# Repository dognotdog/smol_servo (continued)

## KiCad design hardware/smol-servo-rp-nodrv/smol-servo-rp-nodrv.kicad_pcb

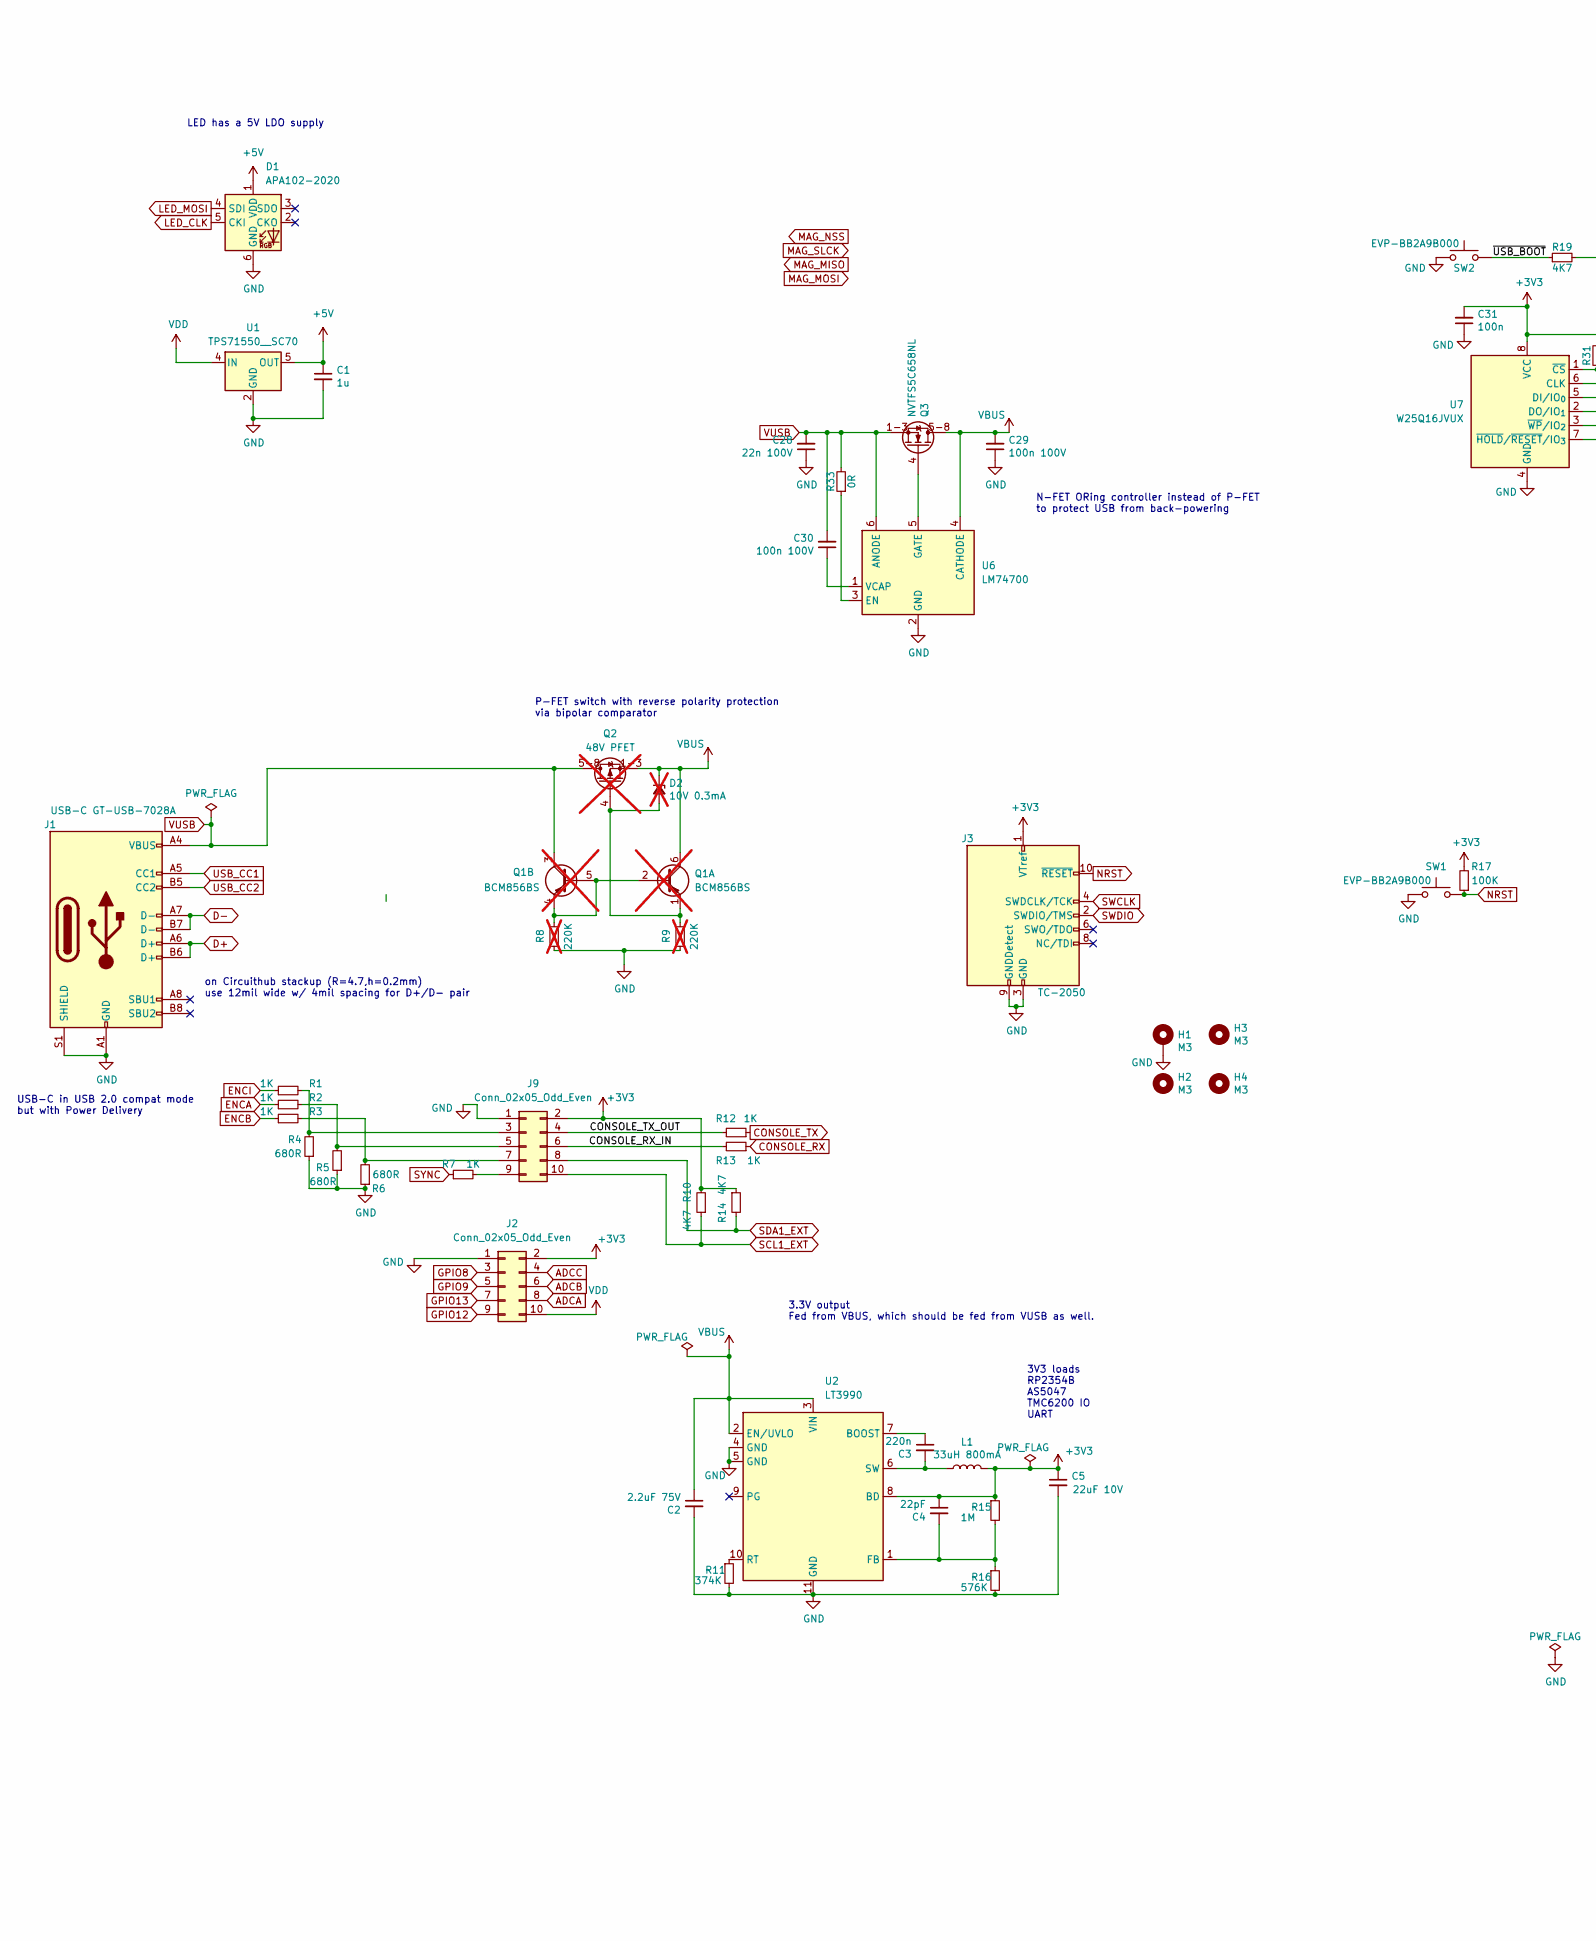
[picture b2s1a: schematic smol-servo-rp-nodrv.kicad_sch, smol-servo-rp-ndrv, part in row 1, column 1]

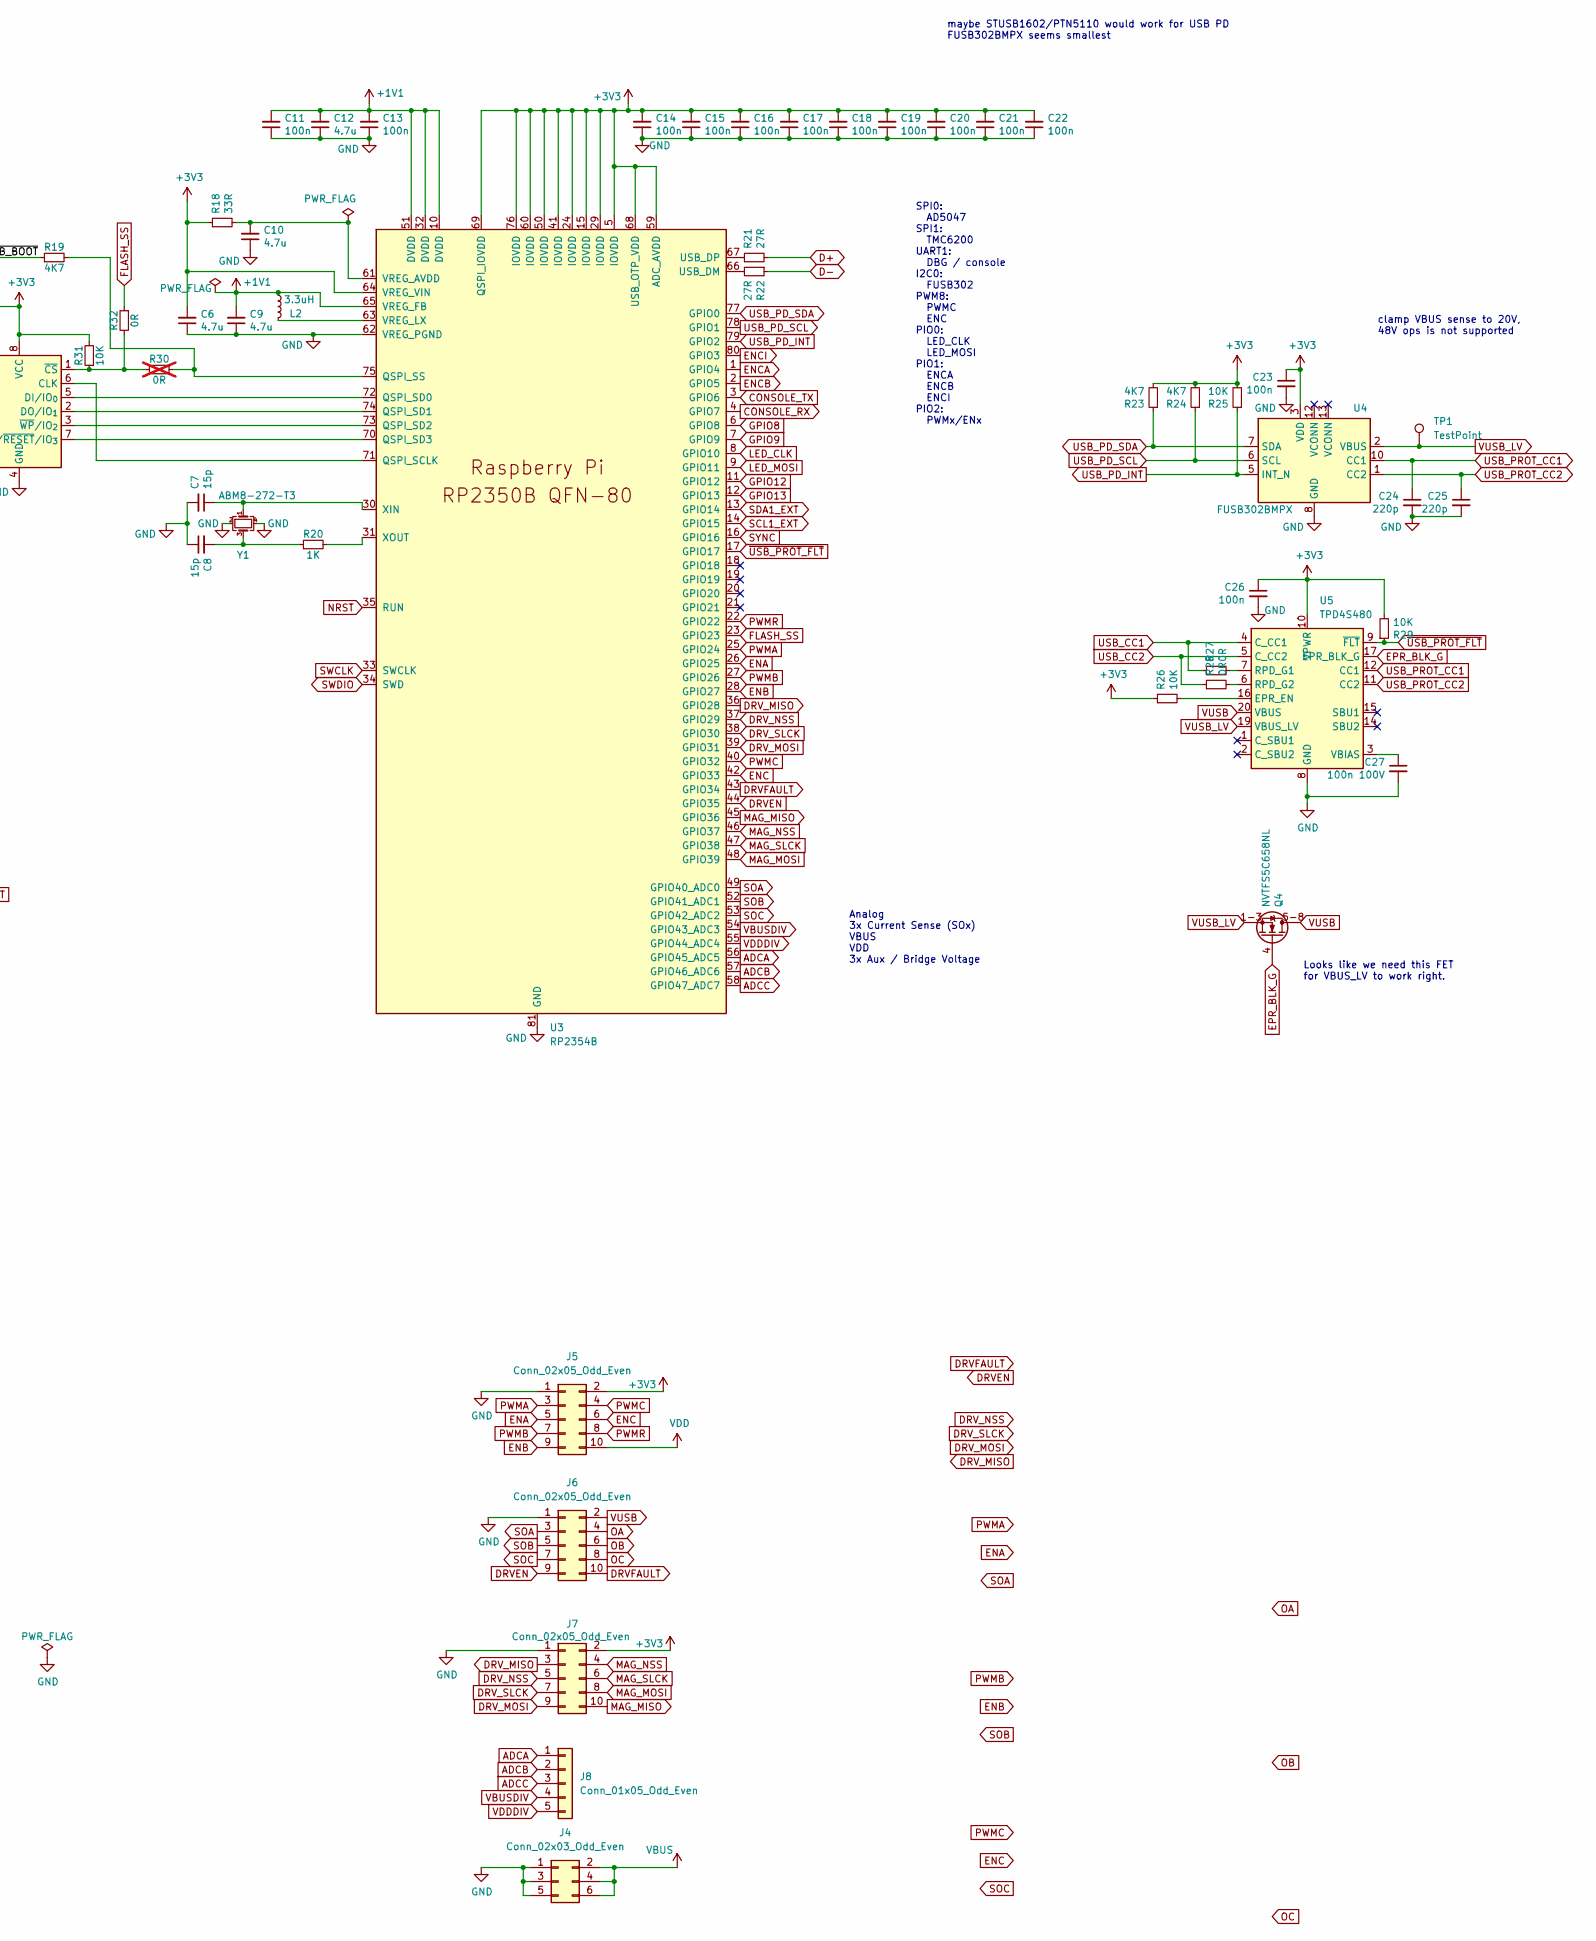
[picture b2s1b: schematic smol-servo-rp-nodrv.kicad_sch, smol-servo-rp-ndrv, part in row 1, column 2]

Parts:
C1: 1u; C_0402_1005Metric; MPN CC0402KRX5R8BB105; JLCPCB C14445
C2: 2.2uF 75V; C_0805_2012Metric; MPN GRM21BD72A225ME01K; JLCPCB C2981733
C3: 220n; C_0402_1005Metric; MPN CL05B224KO5NNNC; JLCPCB C16772
C4: 22pF; C_0402_1005Metric; MPN CL05C220JB5NNNC; JLCPCB C1555
C5: 22uF 10V; C_0603_1608Metric; MPN CM105X5R226M16AT;CL10A226MP8NUNE; JLCPCB C84419
C6, C9, C10, C12: 4.7u; C_0402_1005Metric; MPN CC0402MRX5R6BB475; JLCPCB C23733
C7, C8: 15p; C_0402_1005Metric; MPN CC0402JRNPO8BN150; JLCPCB C106997
C11, C13, C14, C15, C16, C17, C18, C19, C20, C21, C22, C23, C26, C31: 100n; C_0402_1005Metric; MPN CC0402KRX5R8BB104; JLCPCB C5137468
C24, C25: 220p; C_0402_1005Metric; MPN CC0402KRX5R8BB224; JLCPCB C39122
C27, C29: 100n 100V; C_0402_1005Metric; MPN CC0402KRX5R8BB104; JLCPCB C5137468
C28: 22n 100V; C_0402_1005Metric; MPN GMC04X7R223K100NT; JLCPCB C3909603
C30: 100n 100V; C_0402_1005Metric; MPN GRM155R62A104KE14D; JLCPCB C162178
D1: APA102-2020; LED-APA102-2020; MPN BB-2020BGR-TRB; JLCPCB C22439302
D2: 10V 0.3mA; D_0402_1005Metric; MPN CZRQR10VB-HF;PZU10B2L,315; JLCPCB C553572; not fitted
H1: M3; MountingHole_3.2mm_M3_DIN965_Pad
H2, H3, H4: M3; MountingHole_3.2mm_M3
J1: USB-C GT-USB-7028A; USB_C_Receptacle_GT-USB-7028A; MPN GT-USB-7028A; JLCPCB C3001279
J2, J5, J6, J7, J9: Conn_02x05_Odd_Even; PinHeader_2x05_P2.54mm_Vertical
J3: TC-2050; Tag-Connect_TC2050-IDC-NL_2x05_P1.27mm_Vertical
J4: Conn_02x03_Odd_Even; PinHeader_2x03_P2.54mm_Vertical
J8: Conn_01x05_Odd_Even; PinHeader_1x05_P2.54mm_Vertical
L1: 33uH 800mA; L_Taiyo-Yuden_NR-40xx; MPN TYS4030330M;MDWK4040T330MM; JLCPCB C2849475
L2: 3.3uH; L_pol_2016; MPN AOTA-B201610S3R3-101-T; JLCPCB C42411119
Q1: BCM856BS; SOT-363_SC-70-6; not fitted
Q2: 48V PFET; WDFN8; not fitted
Q3, Q4: NVTFS5C658NL; WDFN8; MPN NVTFS5C658NL;NTTFS012N10MDTAG; JLCPCB C5208924
R1, R2, R3, R7, R12, R13, R20: 1K; R_0402_1005Metric; MPN RC0402FR-071KL; JLCPCB C11702
R4, R5, R6: 680R; R_0402_1005Metric; MPN RC0402JR-07680RL; JLCPCB C25130
R8, R9: 220K; R_0402_1005Metric; MPN RC0402FR-072R2L; JLCPCB C25767; not fitted
R10, R14, R23, R24: 4K7; R_0402_1005Metric; MPN RC0402FR-074K7L; JLCPCB C25900
R11: 374K; R_0402_1005Metric; MPN RC0402FR-07374KL; JLCPCB C25781
R15: 1M; R_0402_1005Metric; MPN RC0402FR-071ML; JLCPCB C26083
R16: 576K; R_0402_1005Metric; MPN RC0402FR-07576KL; JLCPCB C27012
R17: 100K; R_0402_1005Metric; MPN RC0402FR-07100KL; JLCPCB C25741
R18: 33R; R_0402_1005Metric; MPN RC0402FR-0733RL; JLCPCB C25105
R19: 4K7; R_0402_1005Metric; MPN RC0402FR-074K7L
R21, R22: 27R; R_0402_1005Metric; MPN RC0402FR-0727RL; JLCPCB C25100
R25, R26, R29: 10K; R_0402_1005Metric; MPN RC0402FR-0710KL; JLCPCB C25744
R27, R28, R32, R33: 0R; R_0402_1005Metric
R30: 0R; R_0402_1005Metric; not fitted
R31: 10K; R_0402_1005Metric; MPN RC0402FR-0710KL
SW1, SW2: EVP-BB2A9B000; SW_SPST_EVPBB; MPN EVP-BB2A9B000; JLCPCB C4365176
TP1: TestPoint; TestPoint_Pad_D1.0mm
U1: TPS71550__SC70; SOT-353_SC-70-5; MPN TPS71550; JLCPCB C571193
U2: LT3990; DFN-10-1EP_3x3mm_P0.5mm_EP1.65x2.38mm_ThermalVias; MPN LT3990*DD; JLCPCB C580169
U3: RP2354B; RP2350-QFN-80-1EP_10x10_P0.4mm_EP3.4x3.4mm_ThermalVias; MPN RP2354B; JLCPCB C39843328
U4: FUSB302BMPX; WQFN-14-1EP_2.5x2.5mm_P0.5mm_EP1.45x1.45mm; MPN FUSB302BMPX; JLCPCB C132291
U5: TPD4S480; WQFN-20-1EP_3x3mm_P0.4mm_EP1.7x1.7mm_ThermalVias
U6: LM74700; SOT-23-6
U7: W25Q16JVUX; Winbond_USON-8-1EP_3x2mm_P0.5mm_EP0.2x1.6mm
Y1: ABM8-272-T3; Oscillator_SMD_Abracon_ASE-4Pin_3.2x2.5mm; MPN ABM8-272-T3; JLCPCB C20625731

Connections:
+1V1: C9.2, C11.2, C12.2, C13.2, L2.1, U3.10 (DVDD), U3.32 (DVDD), U3.51 (DVDD), U3.65 (VREG_FB)
+3V3: C4.1, C5.1, C6.2, C14.2, C15.2, C16.2, C17.2, C18.2, C19.2, C20.2, C21.2, C22.2, C23.1, C26.1, C31.2, J2.2, J3.1 (VTref), J5.2, J7.2, J9.2, L1.2, R10.2, R14.1, R15.1, R17.2, R18.1, R23.2, R24.2, R25.2, R26.1, R29.2, R31.2, U2.8 (BD), U3.5 (IOVDD), U3.15 (IOVDD), U3.24 (IOVDD), U3.29 (IOVDD), U3.41 (IOVDD), U3.50 (IOVDD), U3.59 (ADC_AVDD), U3.60 (IOVDD), U3.64 (VREG_VIN), U3.68 (USB_OTP_VDD), U3.69 (QSPI_IOVDD), U3.76 (IOVDD), U4.3 (VDD), U4.4 (VDD), U5.10 (VPWR), U7.8 (VCC)
+5V: C1.1, D1.1 (VDD), U1.5 (OUT)
/CONSOLE_RX_IN: J9.6, R13.2
/CONSOLE_TX_OUT: J9.4, R12.2
/~USB_BOOT: R19.1, SW2.2
ADCA: J2.8, J8.1, U3.56 (GPIO45_ADC5)
ADCB: J2.6, J8.2, U3.57 (GPIO46_ADC6)
ADCC: J2.4, J8.3, U3.58 (GPIO47_ADC7)
CONSOLE_RX: R13.1, U3.4 (GPIO7)
CONSOLE_TX: R12.1, U3.3 (GPIO6)
D+: J1.A6 (D+), J1.B6 (D+), R21.2
D-: J1.A7 (D-), J1.B7 (D-), R22.1
DRVEN: J6.9, U3.44 (GPIO35)
DRVFAULT: J6.10, U3.43 (GPIO34)
DRV_MISO: J7.3, U3.36 (GPIO28)
DRV_MOSI: J7.9, U3.39 (GPIO31)
DRV_NSS: J7.5, U3.37 (GPIO29)
DRV_SLCK: J7.7, U3.38 (GPIO30)
ENA: J5.5, U3.26 (GPIO25)
ENB: J5.9, U3.28 (GPIO27)
ENC: J5.6, U3.42 (GPIO33)
ENCA: R2.1, U3.1 (GPIO4)
ENCB: R3.1, U3.2 (GPIO5)
ENCI: R1.1, U3.80 (GPIO3)
EPR_BLK_G: Q4.4 (G), U5.17 (EPR_BLK_G)
FLASH_SS: R32.1, U3.23 (GPIO23)
GND: C1.2, C2.2, C5.2, C6.1, C7.2, C8.1, C9.1, C10.1, C11.1, C12.1, C13.1, C14.1, C15.1, C16.1, C17.1, C18.1, C19.1, C20.1, C21.1, C22.1, C23.2, C24.2, C25.2, C26.2, C27.2, C28.1, C29.1, C31.1, D1.6 (GND), H1.1, J1.A1 (GND), J1.A12 (GND), J1.B1 (GND), J1.B12 (GND), J1.S1 (SHIELD), J2.1, J3.3 (GND), J3.5 (GND), J3.9 (GNDDetect), J4.1, J4.3, J4.5, J5.1, J6.1, J7.1, J9.1, R4.1, R5.1, R6.1, R8.2, R9.2, R11.2, R16.2, SW1.1, SW2.1, U1.2 (GND), U2.4 (GND), U2.5 (GND), U2.11 (GND), U3.62 (VREG_PGND), U3.81 (GND), U4.8 (GND), U4.9 (GND), U4.15 (GND), U5.8 (GND), U5.13 (GND), U5.18 (GND), U5.21 (GND), U6.2 (GND), U7.4 (GND), Y1.2, Y1.4
GPIO8: J2.3, U3.6 (GPIO8)
GPIO9: J2.5, U3.7 (GPIO9)
GPIO12: J2.9, U3.11 (GPIO12)
GPIO13: J2.7, U3.12 (GPIO13)
LED_CLK: D1.5 (CKI), U3.8 (GPIO10)
LED_MOSI: D1.4 (SDI), U3.9 (GPIO11)
MAG_MISO: J7.10, U3.45 (GPIO36)
MAG_MOSI: J7.8, U3.48 (GPIO39)
MAG_NSS: J7.4, U3.46 (GPIO37)
MAG_SLCK: J7.6, U3.47 (GPIO38)
NRST: J3.10 (~RESET), R17.1, SW1.2, U3.35 (RUN)
unnamed: C8.2, R20.1, Y1.3
unnamed: D2.2 (A), Q1.1 (E1), Q2.4 (G), R9.1
unnamed: J9.3, R1.2, R4.2
unnamed: J9.5, R2.2, R5.2
unnamed: J9.7, R3.2, R6.2
unnamed: J9.9, R7.2
unnamed: Q1.2 (B1), Q1.4 (E2), Q1.5 (B2), R8.1
unnamed: Q3.4 (G), U6.5 (GATE)
unnamed: C3.1, U2.7 (BOOST)
unnamed: C4.2, R15.2, R16.1, U2.1 (FB)
unnamed: R11.1, U2.10 (RT)
unnamed: C3.2, L1.1, U2.6 (SW)
unnamed: U3.71 (QSPI_SCLK), U7.6 (CLK)
unnamed: U3.72 (QSPI_SD0), U7.5 (DI/IO_{0})
unnamed: U3.74 (QSPI_SD1), U7.2 (DO/IO_{1})
unnamed: U3.73 (QSPI_SD2), U7.3 (~WP/IO_{2})
unnamed: U3.70 (QSPI_SD3), U7.7 (~HOLD/~RESET/IO_{3})
unnamed: R19.2, R30.2, U3.75 (QSPI_SS)
unnamed: R22.2, U3.66 (USB_DM)
unnamed: R21.1, U3.67 (USB_DP)
unnamed: C10.2, R18.2, U3.61 (VREG_AVDD)
unnamed: L2.2, U3.63 (VREG_LX)
unnamed: C7.1, U3.30 (XIN), Y1.1
unnamed: R20.2, U3.31 (XOUT)
unnamed: R26.2, U5.16 (EPR_EN)
unnamed: R27.2, U5.7 (RPD_G1)
unnamed: R28.2, U5.6 (RPD_G2)
unnamed: C27.1, U5.3 (VBIAS)
unnamed: R33.1, U6.3 (EN)
unnamed: C30.1, U6.1 (VCAP)
unnamed: R30.1, R31.1, R32.2, U7.1 (~CS)
OA: J6.4
OB: J6.6
OC: J6.8
PWMA: J5.3, U3.25 (GPIO24)
PWMB: J5.7, U3.27 (GPIO26)
PWMC: J5.4, U3.40 (GPIO32)
PWMR: J5.8, U3.22 (GPIO22)
SCL1_EXT: J9.10, R10.1, U3.14 (GPIO15)
SDA1_EXT: J9.8, R14.2, U3.13 (GPIO14)
SOA: J6.3, U3.49 (GPIO40_ADC0)
SOB: J6.5, U3.52 (GPIO41_ADC1)
SOC: J6.7, U3.53 (GPIO42_ADC2)
SWCLK: J3.4 (SWDCLK/TCK), U3.33 (SWCLK)
SWDIO: J3.2 (SWDIO/TMS), U3.34 (SWD)
SYNC: R7.1, U3.16 (GPIO16)
USB_CC1: J1.A5 (CC1), R27.1, U5.4 (C_CC1)
USB_CC2: J1.B5 (CC2), R28.1, U5.5 (C_CC2)
USB_PD_INT: R25.1, U3.79 (GPIO2), U4.5 (INT_N)
USB_PD_SCL: R24.1, U3.78 (GPIO1), U4.6 (SCL)
USB_PD_SDA: R23.1, U3.77 (GPIO0), U4.7 (SDA)
USB_PROT_CC1: C24.1, U4.10 (CC1), U4.11 (CC1), U5.12 (CC1)
USB_PROT_CC2: C25.1, U4.1 (CC2), U4.14 (CC2), U5.11 (CC2)
VBUS: C2.1, C29.2, D2.1 (K), J4.2, J4.4, J4.6, Q1.6 (C1), Q2.1-3 (S), Q3.5-8 (D), U2.2 (EN/UVLO), U2.3 (VIN), U6.4 (CATHODE)
VBUSDIV: J8.4, U3.54 (GPIO43_ADC3)
VDD: J2.10, J5.10, U1.4 (IN)
VDDDIV: J8.5, U3.55 (GPIO44_ADC4)
VUSB: C28.2, C30.2, J1.A4 (VBUS), J1.A9 (VBUS), J1.B4 (VBUS), J1.B9 (VBUS), J6.2, Q1.3 (C2), Q2.5-8 (D), Q3.1-3 (S), Q4.5-8 (D), R33.2, U5.20 (VBUS), U6.6 (ANODE)
VUSB_LV: Q4.1-3 (S), TP1.1, U4.2 (VBUS), U5.19 (VBUS_LV)
~USB_PROT_FLT: R29.1, U3.17 (GPIO17), U5.9 (~FLT)

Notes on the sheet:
3.3V output Fed from VBUS, which should be fed from VUSB as well.
Looks like we need this FET for VBUS_LV to work right.
maybe STUSB1602/PTN5110 would work for USB PD FUSB302BMPX seems smallest
P-FET switch with reverse polarity protection via bipolar comparator
3V3 loads RP2354B AS5047 TMC6200 IO UART
Analog 3x Current Sense (SOx) VBUS VDD 3x Aux / Bridge Voltage
SPI0: AD5047 SPI1: TMC6200 UART1: DBG / console I2C0: FUSB302 PWM8: PWMC ENC PIO0: LED_CLK LED_MOSI PIO1: ENCA ENCB ENCI PIO2: PWMx/ENx
clamp VBUS sense to 20V, 48V ops is not supported
N-FET ORing controller instead of P-FET to protect USB from back-powering
on Circuithub stackup (R=4.7,h=0.2mm) use 12mil wide w/ 4mil spacing for D+/D- pair
LED has a 5V LDO supply
USB-C in USB 2.0 compat mode but with Power Delivery

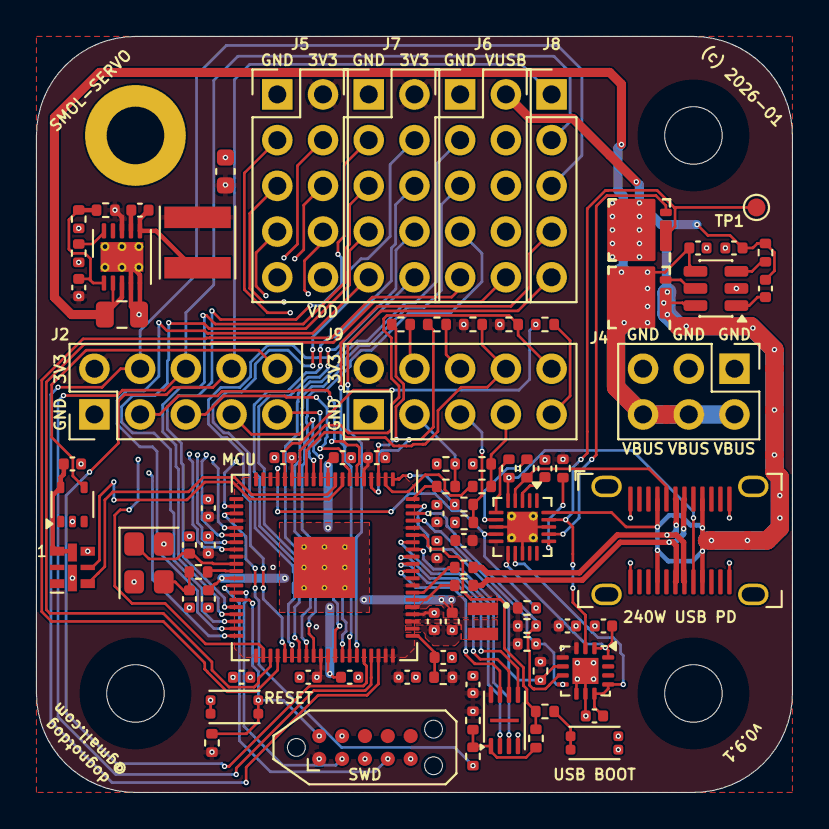
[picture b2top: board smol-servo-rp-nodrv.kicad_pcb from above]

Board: 4 copper layers, 42.0 x 42.0 mm, 91 parts (0 on the bottom side), 94 nets.

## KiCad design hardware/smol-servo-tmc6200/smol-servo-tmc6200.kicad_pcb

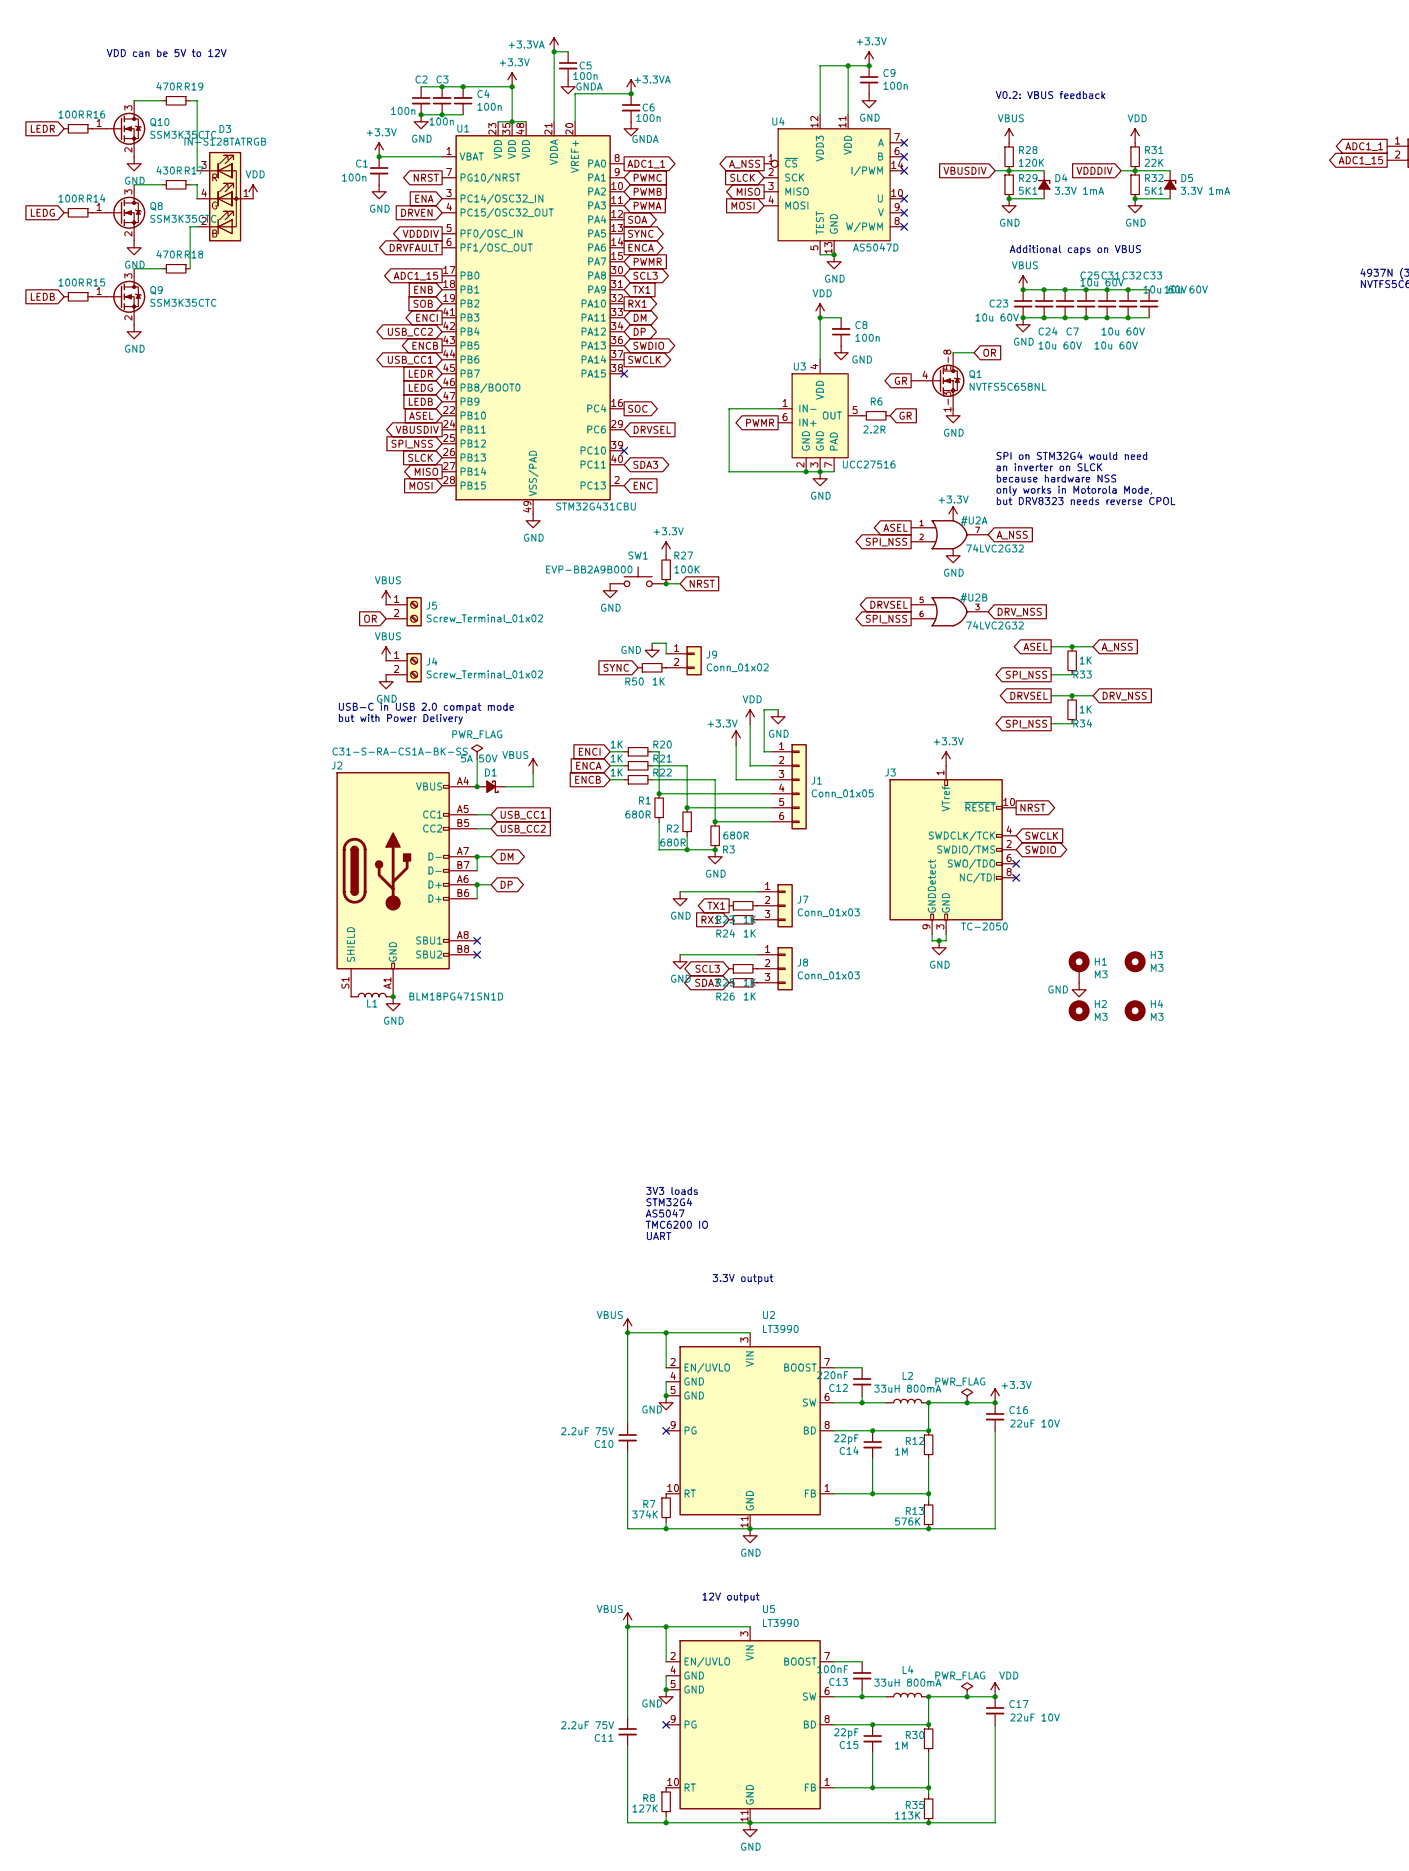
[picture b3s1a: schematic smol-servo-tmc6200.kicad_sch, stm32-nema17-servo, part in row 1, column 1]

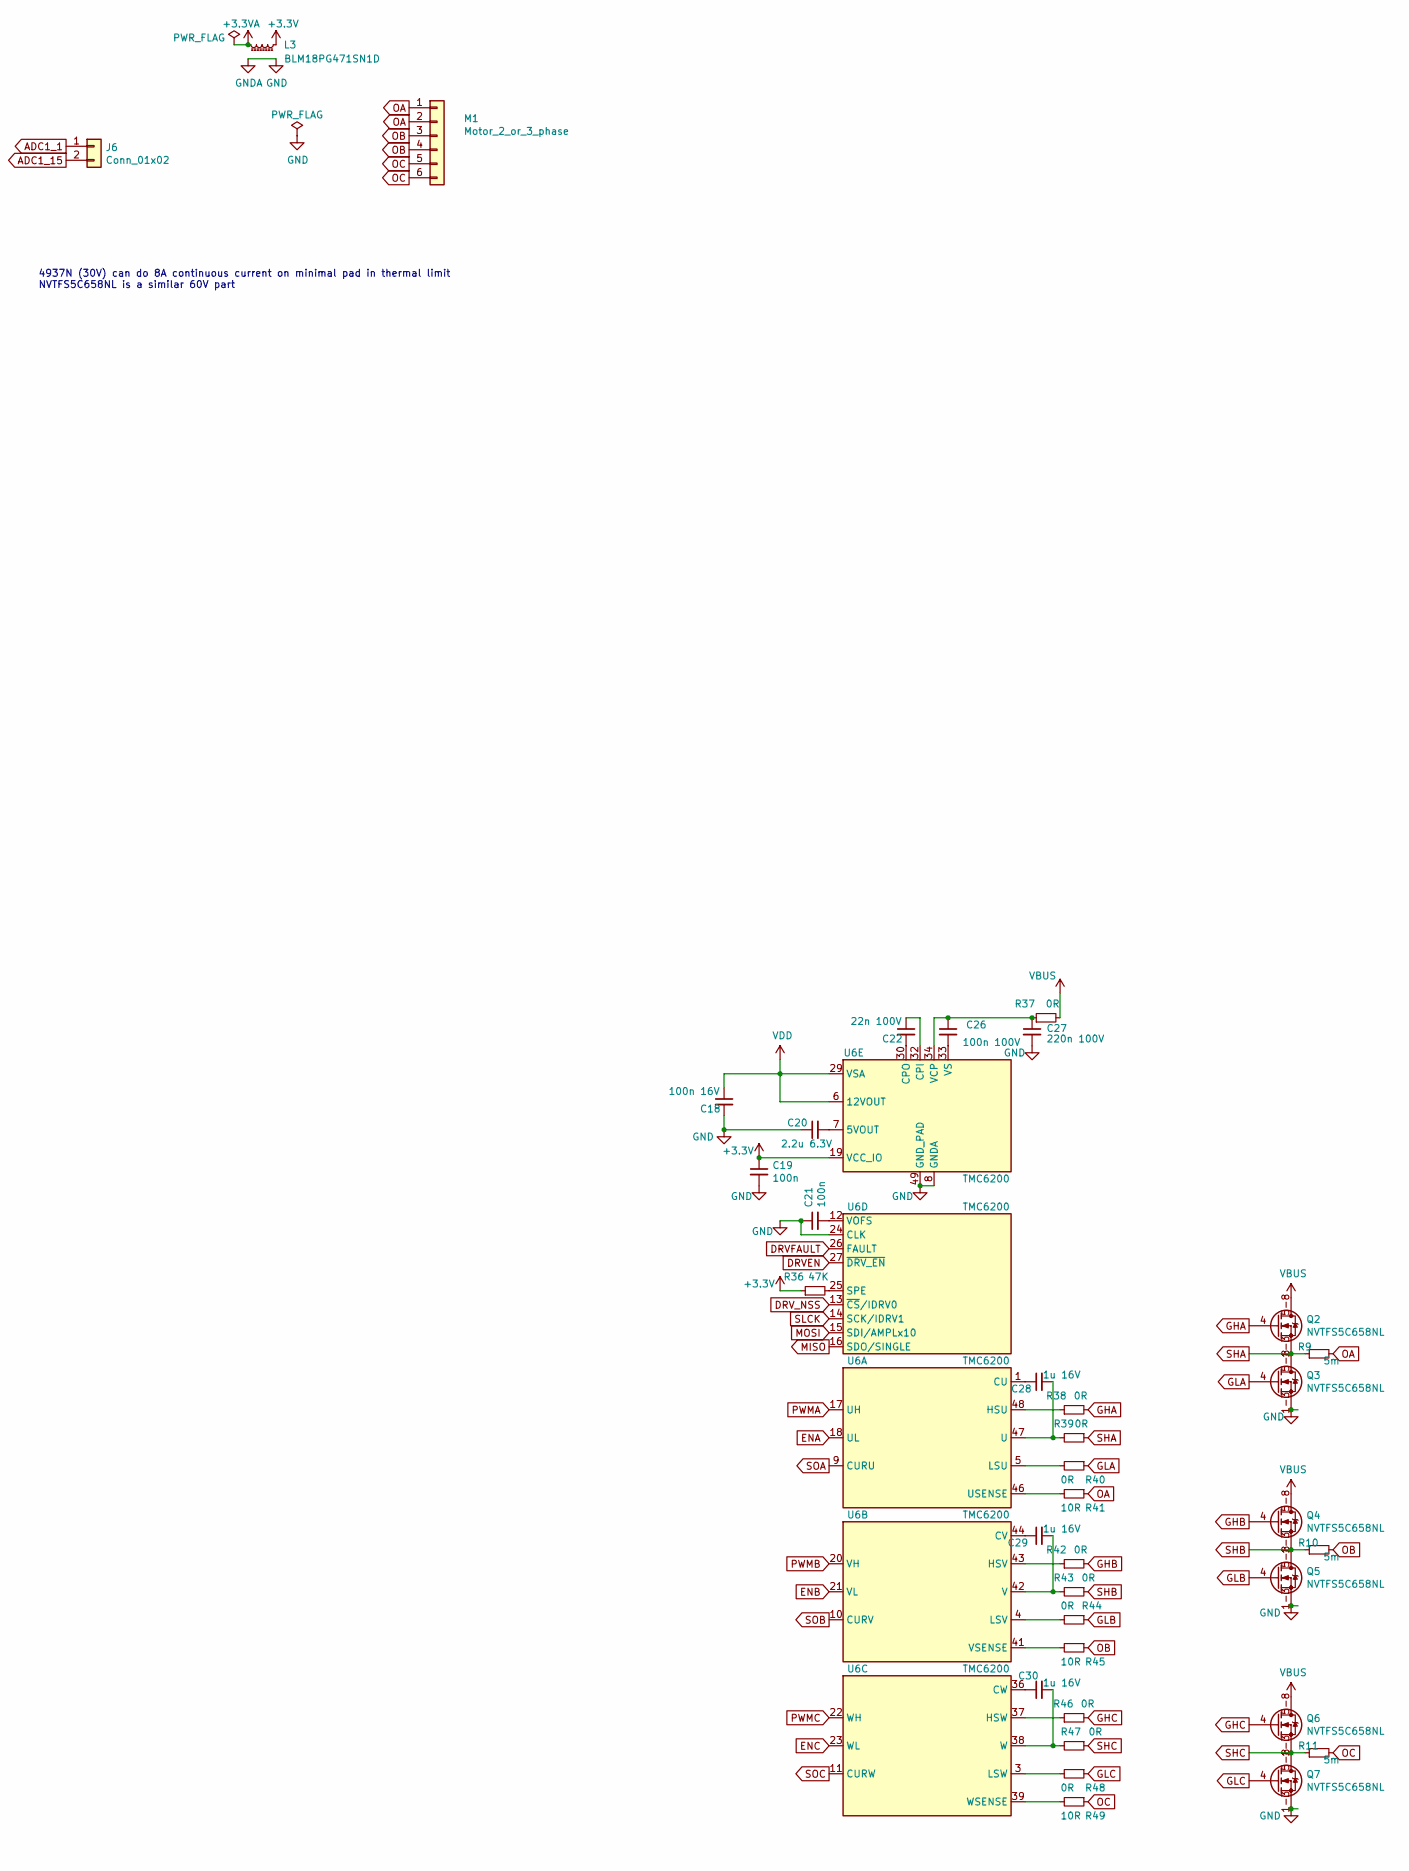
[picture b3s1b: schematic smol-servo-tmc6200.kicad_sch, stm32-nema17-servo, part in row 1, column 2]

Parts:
C1, C2, C3, C4, C5, C6, C8, C9, C19, C21: 100n; C_0402_1005Metric; MPN CC0402KRX5R8BB104
C7, C23, C24, C25, C31, C32, C33: 10u 60V; C_1210_3225Metric; MPN C3225X7R1N106K250AC;CGA6P1X7R1N106M250AC
C10, C11: 2.2uF 75V; C_0805_2012Metric; MPN GRM21BD72A225ME01K
C12: 220nF; C_0402_1005Metric; MPN CL05B224KO5NNNC
C13: 100nF; C_0402_1005Metric; MPN CC0402KRX5R8BB104
C14, C15: 22pF; C_0402_1005Metric; MPN CL05C220JB5NNNC
C16, C17: 22uF 10V; C_0603_1608Metric; MPN CM105X5R226M16AT;CL10A226MP8NUNE
C18: 100n 16V; C_0402_1005Metric; MPN CC0402KRX5R8BB104
C20: 2.2u 6.3V; C_0402_1005Metric; MPN GRM155C80J225KE95D
C22: 22n 100V; C_0603_1608Metric; MPN C1608X7R2A223K080AA
C26: 100n 100V; C_0402_1005Metric; MPN GRM155R62A104ME14D
C27: 220n 100V; C_0603_1608Metric; MPN HMK107C7224KAHTE
C28, C29, C30: 1u 16V; C_0402_1005Metric; MPN CL05A105KO5NNNC
D1: 5A 50V; Diode-SMPA-DO-221BC; MPN V8PAM10S-M3/H
D3: IN-S128TATRGB; LED_Kingbright_AAA3528ESGCT; MPN IN-S128TATRGB
D4, D5: 3.3V 1mA; D_0402_1005Metric; MPN CZRQR3V3B-HF
H1: M3; MountingHole_3.2mm_M3_DIN965_Pad
H2, H3, H4: M3; MountingHole_3.2mm_M3
J1: Conn_01x05; PinHeader_1x06_P2.54mm_Vertical
J2: C31-S-RA-CS1A-BK-SS; USB_C_Receptacle_Adam_C31-S-RA-CS1X-BK; MPN C31-S-RA-CS1A-BK-SS;C31-S-RA-CS1E-BK-SS
J3: TC-2050; Tag-Connect_TC2050-IDC-NL_2x05_P1.27mm_Vertical
J4, J5: Screw_Terminal_01x02; TerminalBlock_Phoenix_PT-1,5-2-3.5-H_1x02_P3.50mm_Horizontal
J6, J9: Conn_01x02; PinHeader_1x02_P2.54mm_Vertical
J7, J8: Conn_01x03; PinHeader_1x03_P2.54mm_Vertical
L1, L3: BLM18PG471SN1D; L_0603_1608Metric; MPN BLM18PG471SN1D
L2, L4: 33uH 800mA; L_Taiyo-Yuden_NR-40xx; MPN TYS4030330M;MDWK4040T330MM
M1: Motor_2_or_3_phase; PinHeader_1x06_P2.54mm_Vertical
Q1, Q2, Q3, Q4, Q5, Q6, Q7: NVTFS5C658NL; WDFN8; MPN NVTFS5C658NL;NTTFS012N10MDTAG
Q8, Q9, Q10: SSM3K35CTC; SOT-883; MPN SSM3K35CTC
R1, R2, R3: 680R; R_0402_1005Metric; MPN RC0402JR-07680RL
R6: 2.2R; R_0402_1005Metric; MPN RC0402FR-072R2L
R7: 374K; R_0402_1005Metric; MPN RC0402FR-07374KL
R8: 127K; R_0402_1005Metric; MPN RC0402FR-07127KL
R9, R10, R11: 5m; R_1206_3216Metric; MPN PA1206FRF7W0R005L
R12, R30: 1M; R_0402_1005Metric; MPN RC0402FR-071ML
R13: 576K; R_0402_1005Metric; MPN RC0402FR-07576KL
R14, R15, R16: 100R; R_0402_1005Metric; MPN RC0402FR-07100RL
R17: 430R; R_0402_1005Metric; MPN RC0402FR-07430RL
R18, R19: 470R; R_0402_1005Metric; MPN RC0402FR-07470RL
R20, R21, R22, R23, R24, R25, R26, R33, R34, R50: 1K; R_0402_1005Metric; MPN RC0402FR-071KL
R27: 100K; R_0402_1005Metric; MPN RC0402FR-07100KL
R28: 120K; R_0402_1005Metric; MPN RC0402FR-07120KL
R29, R32: 5K1; R_0402_1005Metric; MPN RC0402FR-075K11L
R31: 22K; R_0402_1005Metric; MPN RC0402FR-0722KL
R35: 113K; R_0402_1005Metric; MPN RC0402FR-07113KL
R36: 47K; R_0402_1005Metric; MPN RC0402FR-0747KL
R37, R38, R39, R40, R42, R43, R44, R46, R47, R48: 0R; R_0402_1005Metric; MPN RC0402FR-070RL
R41, R45, R49: 10R; R_0402_1005Metric; MPN RC0402FR-0710RL
SW1: EVP-BB2A9B000; SW_SPST_EVPBB; MPN EVP-BB2A9B000
U1: STM32G431CBU; QFN-48-1EP_7x7mm_P0.5mm_EP5.6x5.6mm_ThermalVias; MPN STM32G431CBU
U2, U5: LT3990; DFN-10-1EP_3x3mm_P0.5mm_EP1.65x2.38mm_ThermalVias
U3: UCC27516; Texas_PWSON-N6; MPN UCC27516
U4: AS5047D; TSSOP-14_4.4x5mm_P0.65mm-inlaid; MPN AS5047D
U6: TMC6200; TQFP-48-1EP_7x7mm_P0.5mm_EP5x5mm_ThermalVias

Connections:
+3.3VA: C5.1, C6.1, L3.2, U1.20 (VREF+), U1.21 (VDDA)
ADC1_1: J6.1, U1.8 (PA0)
ADC1_15: J6.2, U1.17 (PB0)
DM: J2.A7 (D-), J2.B7 (D-), U1.33 (PA11)
DP: J2.A6 (D+), J2.B6 (D+), U1.34 (PA12)
DRVEN: U1.4 (PC15/OSC32_OUT), U6.27 (~DRV_EN)
DRVFAULT: U1.6 (PF1/OSC_OUT), U6.26 (FAULT)
ENA: U1.3 (PC14/OSC32_IN), U6.18 (UL)
ENB: U1.18 (PB1), U6.21 (VL)
ENC: U1.2 (PC13), U6.23 (WL)
ENCA: R21.1, U1.14 (PA6)
ENCB: R22.1, U1.43 (PB5)
ENCI: R20.1, U1.41 (PB3)
GHA: Q2.4 (G), R38.2
GHB: Q4.4 (G), R42.2
GHC: Q6.4 (G), R46.2
GLA: Q3.4 (G), R40.1
GLB: Q5.4 (G), R44.1
GLC: Q7.4 (G), R48.1
GR: Q1.4 (G), R6.1
LEDB: R15.2, U1.47 (PB9)
LEDG: R14.2, U1.46 (PB8/BOOT0)
LEDR: R16.2, U1.45 (PB7)
MISO: U1.27 (PB14), U4.3 (MISO), U6.16 (SDO/SINGLE)
MOSI: U1.28 (PB15), U4.4 (MOSI), U6.15 (SDI/AMPLx10)
NRST: J3.10 (~RESET), R27.1, SW1.2, U1.7 (PG10/NRST)
unnamed: C12.1, U2.7 (BOOST)
unnamed: C12.2, L2.1, U2.6 (SW)
unnamed: C13.1, U5.7 (BOOST)
unnamed: C13.2, L4.1, U5.6 (SW)
unnamed: C14.2, R12.2, R13.1, U2.1 (FB)
unnamed: C15.2, R30.2, R35.1, U5.1 (FB)
unnamed: C20.2, U6.7 (5VOUT)
unnamed: C21.2, U6.12 (VOFS)
unnamed: C22.1, U6.32 (CPI)
unnamed: C22.2, U6.30 (CPO)
unnamed: C26.1, C27.1, R37.1, U6.34 (VCP)
unnamed: C26.2, U6.33 (VS)
unnamed: C28.1, U6.1 (CU)
unnamed: C28.2, R39.2, U6.47 (U)
unnamed: C29.1, U6.44 (CV)
unnamed: C29.2, R43.2, U6.42 (V)
unnamed: C30.1, U6.36 (CW)
unnamed: C30.2, R47.2, U6.38 (W)
unnamed: D1.2 (A), J2.A4 (VBUS), J2.A9 (VBUS), J2.B4 (VBUS), J2.B9 (VBUS)
unnamed: D3.2 (BK), R18.1
unnamed: D3.3 (RK), R19.1
unnamed: D3.4 (GK), R17.1
unnamed: J1.4, R1.2, R20.2
unnamed: J1.5, R2.2, R21.2
unnamed: J1.6, R3.2, R22.2
unnamed: J2.S1 (SHIELD), L1.1
unnamed: J7.2, R23.2
unnamed: J7.3, R24.2
unnamed: J8.2, R25.2
unnamed: J8.3, R26.2
unnamed: J9.2, R50.2
unnamed: Q8.1 (G), R14.1
unnamed: Q8.3 (D), R17.2
unnamed: Q9.1 (G), R15.1
unnamed: Q9.3 (D), R18.2
unnamed: Q10.1 (G), R16.1
unnamed: Q10.3 (D), R19.2
unnamed: R6.2, U3.5 (OUT)
unnamed: R7.1, U2.10 (RT)
unnamed: R8.1, U5.10 (RT)
unnamed: R36.2, U6.25 (SPE)
unnamed: R38.1, U6.48 (HSU)
unnamed: R40.2, U6.5 (LSU)
unnamed: R41.2, U6.46 (USENSE)
unnamed: R42.1, U6.43 (HSV)
unnamed: R44.2, U6.4 (LSV)
unnamed: R45.2, U6.41 (VSENSE)
unnamed: R46.1, U6.37 (HSW)
unnamed: R48.2, U6.3 (LSW)
unnamed: R49.2, U6.39 (WSENSE)
OA: M1.1, M1.2, R9.2, R41.1
OB: M1.3, M1.4, R10.2, R45.1
OC: M1.5, M1.6, R11.2, R49.1
OR: J5.2, Q1.5-8 (D)
PWMA: U1.11 (PA3), U6.17 (UH)
PWMB: U1.10 (PA2), U6.20 (VH)
PWMC: U1.9 (PA1), U6.22 (WH)
PWMR: U1.15 (PA7), U3.6 (IN+)
RX1: R24.1, U1.32 (PA10)
SCL3: R25.1, U1.30 (PA8)
SDA3: R26.1, U1.40 (PC11)
SHA: Q2.1-3 (S), Q3.5-8 (D), R9.1, R39.1
SHB: Q4.1-3 (S), Q5.5-8 (D), R10.1, R43.1
SHC: Q6.1-3 (S), Q7.5-8 (D), R11.1, R47.1
SLCK: U1.26 (PB13), U4.2 (SCK), U6.14 (SCK/IDRV1)
SOA: U1.12 (PA4), U6.9 (CURU)
SOB: U1.19 (PB2), U6.10 (CURV)
SOC: U1.16 (PC4), U6.11 (CURW)
SWCLK: J3.4 (SWDCLK/TCK), U1.37 (PA14)
SWDIO: J3.2 (SWDIO/TMS), U1.36 (PA13)
SYNC: R50.1, U1.13 (PA5)
TX1: R23.1, U1.31 (PA9)
USB_CC1: J2.A5 (CC1), U1.44 (PB6)
USB_CC2: J2.B5 (CC2), U1.42 (PB4)
VBUS: C7.1, C10.1, C11.1, C23.1, C24.1, C25.1, C31.1, C32.1, C33.1, D1.1 (K), J4.1, J5.1, Q2.5-8 (D), Q4.5-8 (D), Q6.5-8 (D), R28.1, R37.2, U2.2 (EN/UVLO), U2.3 (VIN), U5.2 (EN/UVLO), U5.3 (VIN)
VBUSDIV: D4.1 (K), R28.2, R29.1, U1.24 (PB11)
VDD: C8.2, C15.1, C17.1, C18.1, D3.1 (A), J1.2, L4.2, R30.1, R31.1, U3.4 (VDD), U5.8 (BD), U6.6 (12VOUT), U6.29 (VSA)
VDDDIV: D5.1 (K), R31.2, R32.1, U1.5 (PF0/OSC_IN)

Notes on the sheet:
3.3V output
Additional caps on VBUS
4937N (30V) can do 8A continuous current on minimal pad in thermal limit NVTFS5C658NL is a similar 60V part
12V output
3V3 loads STM32G4 AS5047 TMC6200 IO UART
V0.2: VBUS feedback
SPI on STM32G4 would need an inverter on SLCK because hardware NSS only works in Motorola Mode, but DRV8323 needs reverse CPOL
VDD can be 5V to 12V
USB-C in USB 2.0 compat mode but with Power Delivery

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
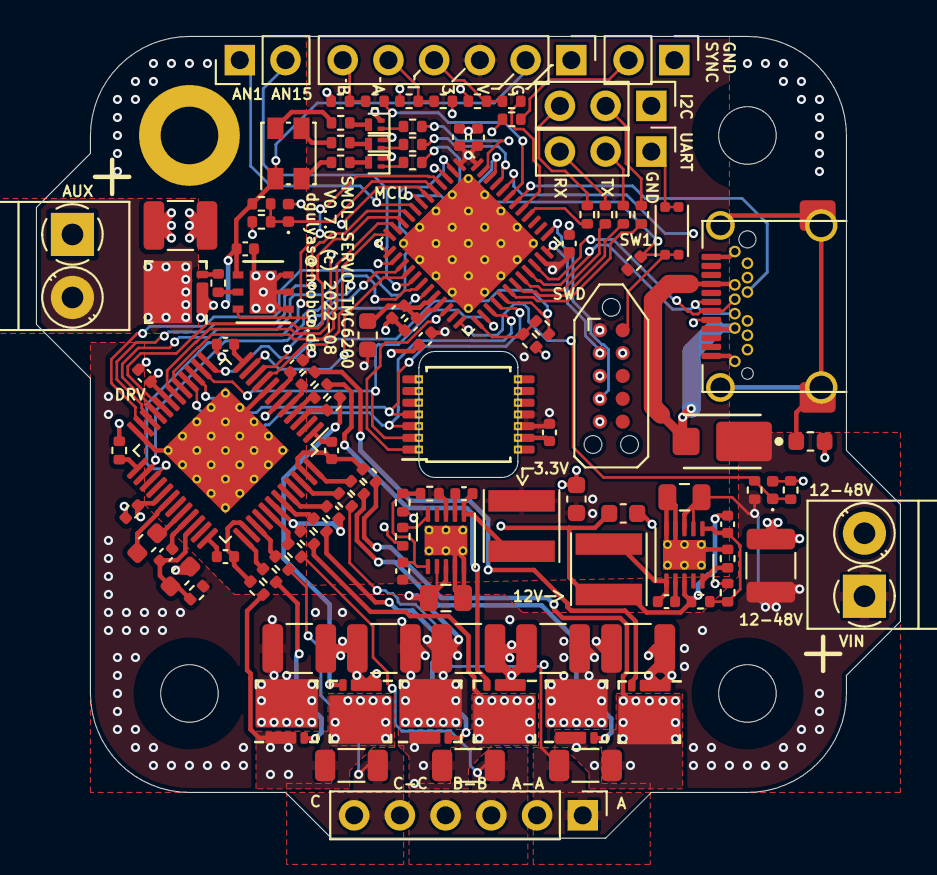
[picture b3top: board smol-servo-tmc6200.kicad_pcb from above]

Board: 4 copper layers, 48.0 x 44.5 mm, 120 parts (0 on the bottom side), 109 nets.
